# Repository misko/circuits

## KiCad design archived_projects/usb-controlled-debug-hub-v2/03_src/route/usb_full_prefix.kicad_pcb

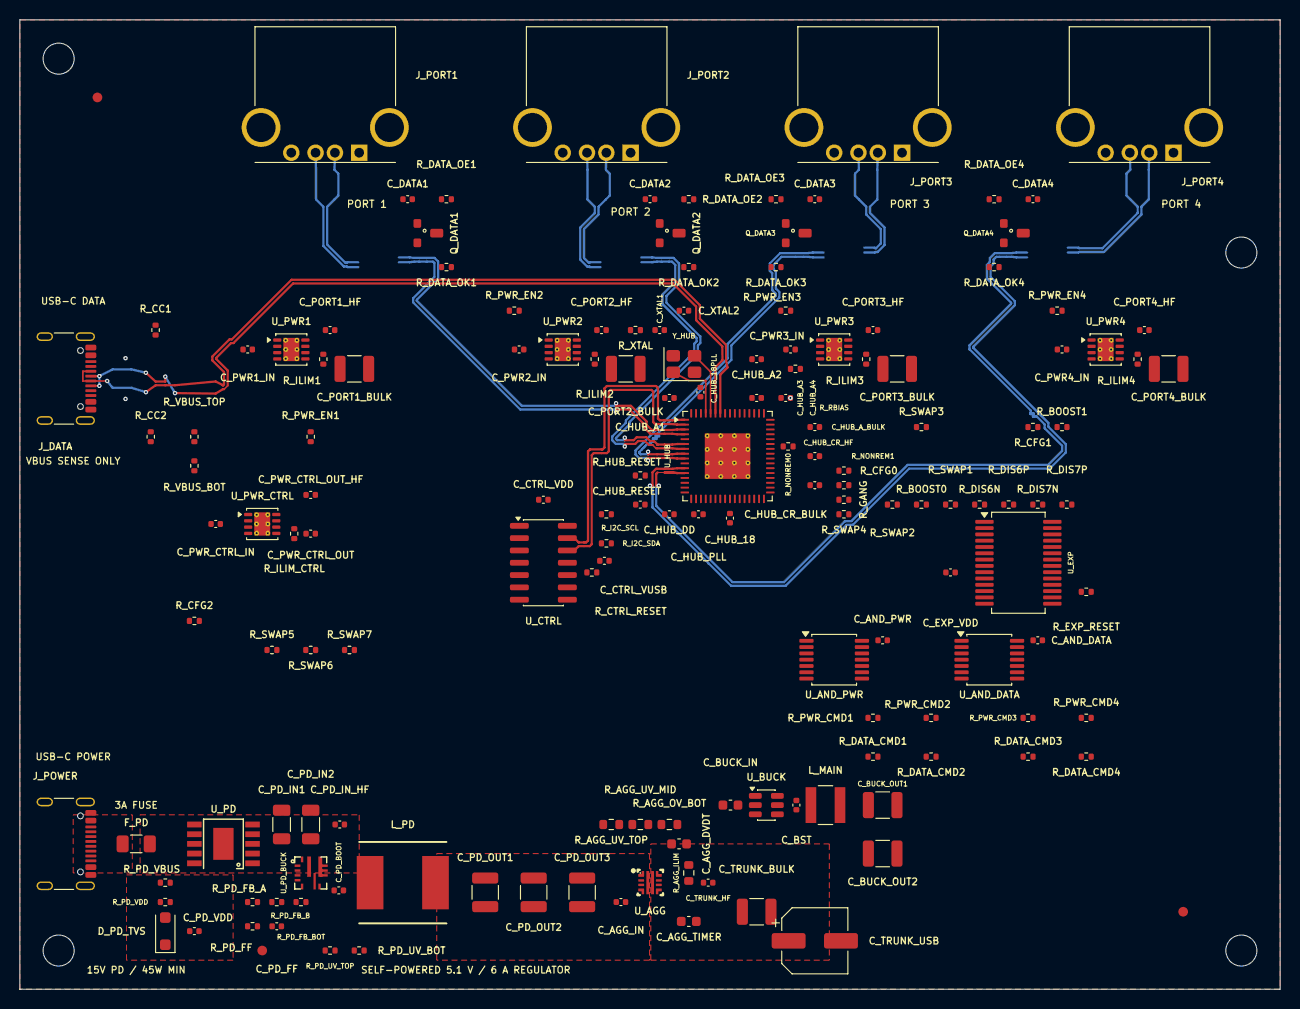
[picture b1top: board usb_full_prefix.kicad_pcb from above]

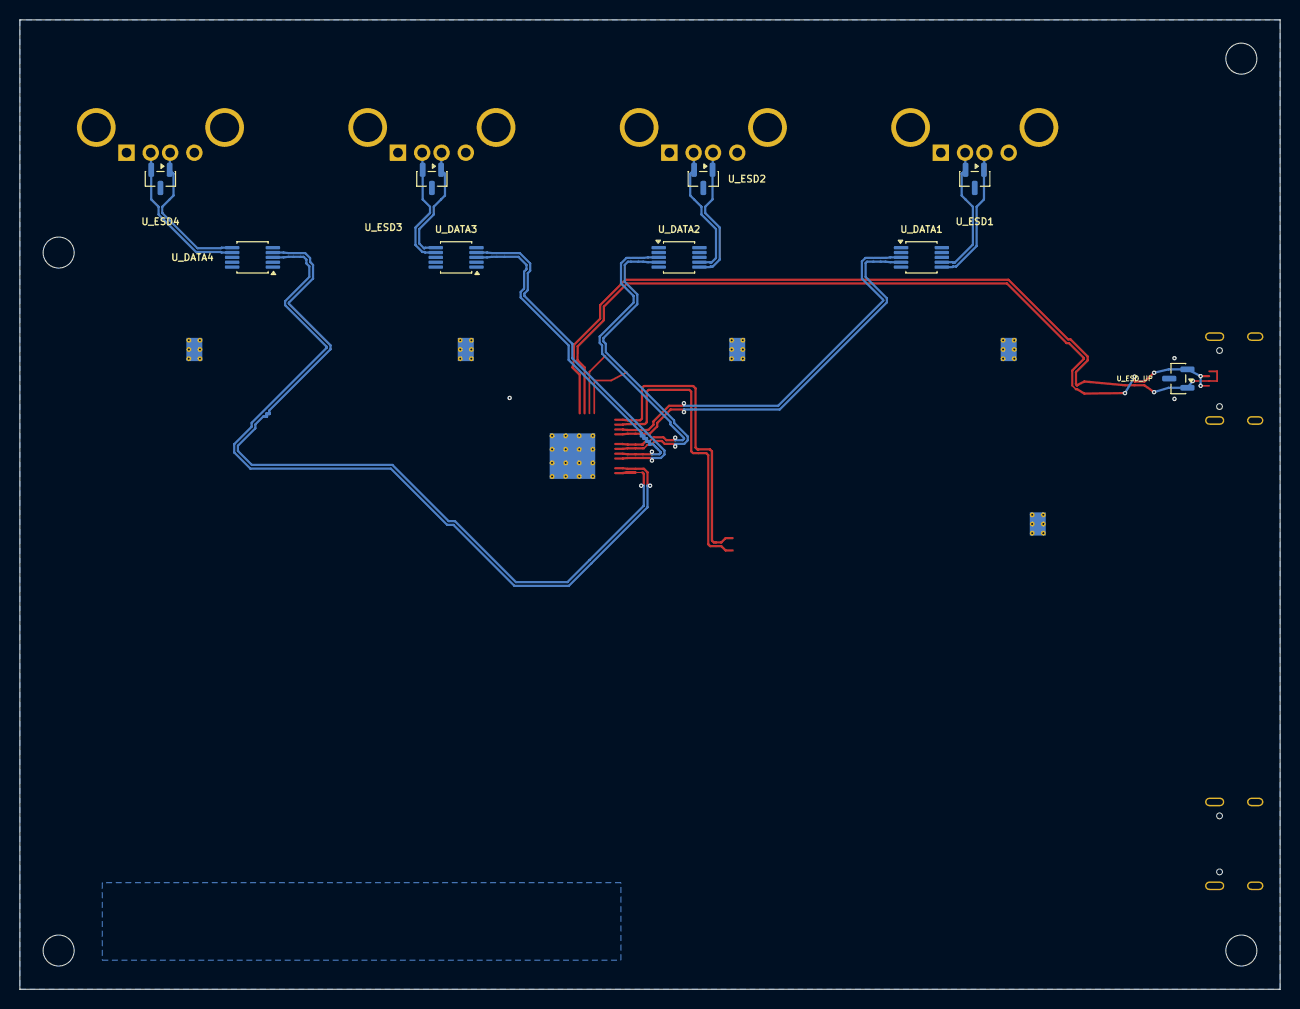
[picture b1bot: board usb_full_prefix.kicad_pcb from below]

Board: 4 copper layers, 130.0 x 100.0 mm, 169 parts (9 on the bottom side), 117 nets.

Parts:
C_AGG_DVDT: 3.3nF; C_0603_1608Metric
C_AGG_IN: 100nF; C_0402_1005Metric
C_AGG_TIMER: 3.3nF; C_0603_1608Metric
C_AND_DATA: 100nF; C_0402_1005Metric
C_AND_PWR: 100nF; C_0402_1005Metric
C_BST: 100nF; C_0402_1005Metric
C_BUCK_IN: 10uF; C_0603_1608Metric
C_BUCK_OUT1, C_BUCK_OUT2: 22uF; C_1210_3225Metric
C_CTRL_VDD: 100nF; C_0402_1005Metric
C_CTRL_VUSB: 330nF; C_0402_1005Metric
C_DATA1, C_DATA2, C_DATA3, C_DATA4: 100nF; C_0402_1005Metric
C_EXP_VDD: 100nF; C_0402_1005Metric
C_HUB_18, C_HUB_18PLL: 1uF; C_0402_1005Metric
C_HUB_A1, C_HUB_A2, C_HUB_A3, C_HUB_A4: 100nF; C_0402_1005Metric
C_HUB_A_BULK: 1uF; C_0402_1005Metric
C_HUB_CR_BULK: 1uF; C_0402_1005Metric
C_HUB_CR_HF: 100nF; C_0402_1005Metric
C_HUB_DD: 100nF; C_0402_1005Metric
C_HUB_PLL: 100nF; C_0402_1005Metric
C_HUB_RESET: 1uF; C_0402_1005Metric
C_PD_BOOT: 100nF; C_0402_1005Metric
C_PD_FF: 100pF; C_0402_1005Metric
C_PD_IN1, C_PD_IN2: 10uF; C_1206_3216Metric
C_PD_IN_HF: 100nF; C_0402_1005Metric
C_PD_OUT1, C_PD_OUT2, C_PD_OUT3: 22uF; C_1210_3225Metric
C_PD_VDD: 1uF; C_0402_1005Metric
C_PORT1_BULK, C_PORT2_BULK, C_PORT3_BULK, C_PORT4_BULK: 22uF; C_1210_3225Metric
C_PORT1_HF, C_PORT2_HF, C_PORT3_HF, C_PORT4_HF: 100nF; C_0402_1005Metric
C_PWR1_IN, C_PWR2_IN, C_PWR3_IN, C_PWR4_IN: 100nF; C_0402_1005Metric
C_PWR_CTRL_IN: 100nF; C_0402_1005Metric
C_PWR_CTRL_OUT: 1uF; C_0402_1005Metric
C_PWR_CTRL_OUT_HF: 100nF; C_0402_1005Metric
C_TRUNK_BULK: 22uF; C_1210_3225Metric
C_TRUNK_HF: 100nF; C_0402_1005Metric
C_TRUNK_USB: 180uF; CP_Elec_6.3x5.8
C_XTAL1, C_XTAL2: 18pF; C_0402_1005Metric
D_PD_TVS: C207257; D_SOD-123F
FID1, FID2, FID3: Fiducial_1mm_Mask2mm
F_PD: C14165; Fuse_1206_3216Metric
H1, H2, H3, H4: MountingHole_3.2mm_M3
J_DATA: C165948; TYPE-C-31-M-12_Datasheet
J_PORT1, J_PORT2, J_PORT3, J_PORT4: C503996; KH-AF90DIP-112_Horizontal
J_POWER: C165948; TYPE-C-31-M-12_Datasheet
L_MAIN: C15269; Sunlord_SWPA4030S
L_PD: C17700166; Sunlord_MWSA0804S
Q_DATA1, Q_DATA2, Q_DATA3, Q_DATA4: C85047; Diodes_SOT23_2N7002K
R_AGG_ILIM: 1kΩ; R_0603_1608Metric
R_AGG_OV_BOT: 43.2kΩ; R_0603_1608Metric
R_AGG_UV_MID: 10kΩ; R_0603_1608Metric
R_AGG_UV_TOP: 150kΩ; R_0603_1608Metric
R_BOOST0, R_BOOST1: 10kΩ; R_0402_1005Metric
R_CC1, R_CC2: 5.1kΩ; R_0402_1005Metric
R_CFG0, R_CFG1, R_CFG2: 10kΩ; R_0402_1005Metric
R_CTRL_RESET: 10kΩ; R_0402_1005Metric
R_DATA_CMD1, R_DATA_CMD2, R_DATA_CMD3, R_DATA_CMD4: 10kΩ; R_0402_1005Metric
R_DATA_OE1, R_DATA_OE2, R_DATA_OE3, R_DATA_OE4: 10kΩ; R_0402_1005Metric
R_DATA_OK1, R_DATA_OK2, R_DATA_OK3, R_DATA_OK4: 10kΩ; R_0402_1005Metric
R_DIS6N, R_DIS6P, R_DIS7N, R_DIS7P: 10kΩ; R_0402_1005Metric
R_EXP_RESET: 10kΩ; R_0402_1005Metric
R_GANG: 10kΩ; R_0402_1005Metric
R_HUB_RESET: 10kΩ; R_0402_1005Metric
R_I2C_SCL, R_I2C_SDA: 4.7kΩ; R_0402_1005Metric
R_ILIM1, R_ILIM2, R_ILIM3, R_ILIM4: 165kΩ; R_0402_1005Metric
R_ILIM_CTRL: 165kΩ; R_0402_1005Metric
R_NONREM0, R_NONREM1: 10kΩ; R_0402_1005Metric
R_PD_FB_A: 75kΩ; R_0402_1005Metric
R_PD_FB_B: 499Ω; R_0402_1005Metric
R_PD_FB_BOT: 10kΩ; R_0402_1005Metric
R_PD_FF: 20kΩ; R_0402_1005Metric
R_PD_UV_BOT: 27.4kΩ; R_0402_1005Metric
R_PD_UV_TOP: 200kΩ; R_0402_1005Metric
R_PD_VBUS: 10kΩ; R_0402_1005Metric
R_PD_VDD: 1kΩ; R_0402_1005Metric
R_PWR_CMD1, R_PWR_CMD2, R_PWR_CMD3, R_PWR_CMD4: 10kΩ; R_0402_1005Metric
R_PWR_EN1, R_PWR_EN2, R_PWR_EN3, R_PWR_EN4: 10kΩ; R_0402_1005Metric
R_RBIAS: 12kΩ; R_0402_1005Metric
R_SWAP1, R_SWAP2, R_SWAP3, R_SWAP4, R_SWAP5, R_SWAP6, R_SWAP7: 100kΩ; R_0402_1005Metric
R_VBUS_BOT: 100kΩ; R_0402_1005Metric
R_VBUS_TOP: 47kΩ; R_0402_1005Metric
R_XTAL: 1MΩ; R_0402_1005Metric
U_AGG: C2864845; TI_RPW0010A_VQFN-HR-10_2x2mm_P0.45mm
U_AND_DATA: C6053; TSSOP-14_4.4x5mm_P0.65mm
U_AND_PWR: C6053; TSSOP-14_4.4x5mm_P0.65mm
U_BUCK: C5248536; TSOT-23-6
U_CTRL: C640876; SOIC-14_3.9x8.7mm_P1.27mm
U_DATA1, U_DATA2, U_DATA3, U_DATA4: C11355; MSOP-10_3x3mm_P0.5mm
U_ESD1, U_ESD2, U_ESD3, U_ESD4: C3708426; SOT-23
U_ESD_UP: C3708426; SOT-23
U_EXP: C558584; SSOP-28_5.3x10.2mm_P0.65mm
U_HUB: C478081; QFN-64-1EP_9x9mm_P0.5mm_EP4.7x4.7mm_ThermalVias
U_PD: C970725; WCH_CH224K_ESSOP10_EP
U_PD_BUCK: C841386; TI_RPA0010A_VQFN-HR-10_3x3mm
U_PWR1, U_PWR2, U_PWR3, U_PWR4: C130056; VSON-8-1EP_3x3mm_P0.65mm_EP1.65x2.4mm_ThermalVias
U_PWR_CTRL: C130056; VSON-8-1EP_3x3mm_P0.65mm_EP1.65x2.4mm_ThermalVias
Y_HUB: C1985204; Crystal_SMD_3225-4Pin_3.2x2.5mm

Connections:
3V3_MAIN: C_AND_DATA.1, C_AND_PWR.1, C_BUCK_OUT1.1, C_BUCK_OUT2.1, C_DATA1.1, C_DATA2.1, C_DATA3.1, C_DATA4.1, C_HUB_A1.1, C_HUB_A2.1, C_HUB_A3.1, C_HUB_A4.1, C_HUB_A_BULK.1, C_HUB_CR_BULK.1, C_HUB_CR_HF.1, C_HUB_DD.1, C_HUB_PLL.1, L_MAIN.2, R_DATA_OE1.1, R_DATA_OE2.1, R_DATA_OE3.1, R_DATA_OE4.1, R_DIS6N.1, R_DIS6P.1, R_DIS7N.1, R_DIS7P.1, R_HUB_RESET.1, R_NONREM0.1, R_SWAP1.2, U_AND_DATA.14, U_AND_PWR.14, U_BUCK.1, U_DATA1.1, U_DATA2.1, U_DATA3.1, U_DATA4.1, U_HUB.5, U_HUB.10, U_HUB.24, U_HUB.46, U_HUB.52, U_HUB.57, U_HUB.64
AGG_DVDT: C_AGG_DVDT.1, U_AGG.7
AGG_ILIM: R_AGG_ILIM.1, U_AGG.9
AGG_OV: R_AGG_OV_BOT.1, R_AGG_UV_MID.2, U_AGG.2
AGG_TIMER: C_AGG_TIMER.1, U_AGG.10
AGG_UV: R_AGG_UV_MID.1, R_AGG_UV_TOP.2, U_AGG.1
BST_3V3: C_BST.1, U_BUCK.6
CTRL_RESET_N: R_CTRL_RESET.2, U_CTRL.4
CTRL_VUSB_3V3: C_CTRL_VUSB.1, U_CTRL.11
DATA_CC1: J_DATA.A5, R_CC1.1
DATA_CC2: J_DATA.B5, R_CC2.1
DATA_CMD1: R_DATA_CMD1.1, U_AND_DATA.2, U_EXP.25
DATA_CMD2: R_DATA_CMD2.1, U_AND_DATA.5, U_EXP.26
DATA_CMD3: R_DATA_CMD3.1, U_AND_DATA.10, U_EXP.27
DATA_CMD4: R_DATA_CMD4.1, U_AND_DATA.13, U_EXP.28
DATA_OE1_N: Q_DATA1.3, R_DATA_OE1.2, U_DATA1.10
DATA_OE2_N: Q_DATA2.3, R_DATA_OE2.2, U_DATA2.10
DATA_OE3_N: Q_DATA3.3, R_DATA_OE3.2, U_DATA3.10
DATA_OE4_N: Q_DATA4.3, R_DATA_OE4.2, U_DATA4.10
DATA_OK1: Q_DATA1.1, R_DATA_OK1.1, U_AND_DATA.3
DATA_OK2: Q_DATA2.1, R_DATA_OK2.1, U_AND_DATA.6
DATA_OK3: Q_DATA3.1, R_DATA_OK3.1, U_AND_DATA.8
DATA_OK4: Q_DATA4.1, R_DATA_OK4.1, U_AND_DATA.11
EXP_RESET_N: R_EXP_RESET.2, U_EXP.18
GND: C_AGG_DVDT.2, C_AGG_IN.2, C_AGG_TIMER.2, C_AND_DATA.2, C_AND_PWR.2, C_BUCK_IN.2, C_BUCK_OUT1.2, C_BUCK_OUT2.2, C_CTRL_VDD.2, C_CTRL_VUSB.2, C_DATA1.2, C_DATA2.2, C_DATA3.2, C_DATA4.2, C_EXP_VDD.2, C_HUB_18.2, C_HUB_18PLL.2, C_HUB_A1.2, C_HUB_A2.2, C_HUB_A3.2, C_HUB_A4.2, C_HUB_A_BULK.2, C_HUB_CR_BULK.2, C_HUB_CR_HF.2, C_HUB_DD.2, C_HUB_PLL.2, C_HUB_RESET.2, C_PD_IN1.2, C_PD_IN2.2, C_PD_IN_HF.2, C_PD_OUT1.2, C_PD_OUT2.2, C_PD_OUT3.2, C_PD_VDD.2, C_PORT1_BULK.2, C_PORT1_HF.2, C_PORT2_BULK.2, C_PORT2_HF.2, C_PORT3_BULK.2, C_PORT3_HF.2, C_PORT4_BULK.2, C_PORT4_HF.2, C_PWR1_IN.2, C_PWR2_IN.2, C_PWR3_IN.2, C_PWR4_IN.2, C_PWR_CTRL_IN.2, C_PWR_CTRL_OUT.2, C_PWR_CTRL_OUT_HF.2, C_TRUNK_BULK.2, C_TRUNK_HF.2, C_TRUNK_USB.2, C_XTAL1.2, C_XTAL2.2, D_PD_TVS.1, J_DATA.A1, J_DATA.A12, J_DATA.B1, J_DATA.B12, J_DATA.SH, J_PORT1.4, J_PORT1.5, J_PORT2.4, J_PORT2.5, J_PORT3.4, J_PORT3.5, J_PORT4.4, J_PORT4.5, J_POWER.A1, J_POWER.A12, J_POWER.B1, J_POWER.B12, J_POWER.SH, Q_DATA1.2, Q_DATA2.2, Q_DATA3.2, Q_DATA4.2, R_AGG_ILIM.2, R_AGG_OV_BOT.2, R_BOOST0.2, R_BOOST1.2, R_CC1.2, R_CC2.2, R_CFG0.2, R_CFG1.2, R_CFG2.2, R_DATA_CMD1.2, R_DATA_CMD2.2, R_DATA_CMD3.2, R_DATA_CMD4.2, R_DATA_OK1.2, R_DATA_OK2.2, R_DATA_OK3.2, R_DATA_OK4.2, R_GANG.2, R_ILIM1.2, R_ILIM2.2, R_ILIM3.2, R_ILIM4.2, R_ILIM_CTRL.2, R_NONREM1.2, R_PD_FB_BOT.2, R_PD_UV_BOT.2, R_PWR_CMD1.2, R_PWR_CMD2.2, R_PWR_CMD3.2, R_PWR_CMD4.2, R_PWR_EN1.2, R_PWR_EN2.2, R_PWR_EN3.2, R_PWR_EN4.2, R_RBIAS.2, R_SWAP2.2, R_SWAP3.2, R_SWAP4.2, R_SWAP5.2, R_SWAP6.2, R_SWAP7.2, R_VBUS_BOT.2, U_AGG.4, U_AGG.8, U_AND_DATA.7, U_AND_PWR.7, U_BUCK.4, U_CTRL.14, U_DATA1.2, U_DATA1.5, U_DATA2.2, U_DATA2.5, U_DATA3.2, U_DATA3.5, U_DATA4.2, U_DATA4.5, U_ESD1.3, U_ESD2.3, U_ESD3.3, U_ESD4.3, U_ESD_UP.3, U_EXP.10, U_EXP.15, U_EXP.16, U_EXP.17, U_HUB.65, U_PD.9, U_PD.11, U_PD_BUCK.3, U_PD_BUCK.9, U_PD_BUCK.10, U_PWR1.1, U_PWR1.9, U_PWR2.1, U_PWR2.9, U_PWR3.1, U_PWR3.9, U_PWR4.1, U_PWR4.9, U_PWR_CTRL.1, U_PWR_CTRL.9, Y_HUB.2, Y_HUB.4
HUB_BOOST0: R_BOOST0.1, U_HUB.50
HUB_BOOST1: R_BOOST1.1, U_HUB.48
HUB_CFG0: R_CFG0.1, U_HUB.41
HUB_CFG1: R_CFG1.1, U_HUB.42
HUB_CFG2: R_CFG2.1, U_HUB.13
HUB_DIS6_N: R_DIS6N.2, U_HUB.53
HUB_DIS6_P: R_DIS6P.2, U_HUB.54
HUB_DIS7_N: R_DIS7N.2, U_HUB.55
HUB_DIS7_P: R_DIS7P.2, U_HUB.56
HUB_GANG: R_GANG.1, U_HUB.34
HUB_NONREM0: R_NONREM0.2, U_HUB.45
HUB_NONREM1: R_NONREM1.1, U_HUB.40
HUB_OCS1_N: U_HUB.28, U_PWR_CTRL.8
HUB_OCS2_N: U_HUB.27, U_PWR1.8
HUB_OCS3_N: U_HUB.22, U_PWR2.8
HUB_OCS4_N: U_HUB.21, U_PWR3.8
HUB_OCS5_N: U_HUB.35, U_PWR4.8
HUB_PRTPWR1: U_HUB.29, U_PWR_CTRL.4
HUB_PRTPWR2: U_AND_PWR.1, U_HUB.26
HUB_PRTPWR3: U_AND_PWR.4, U_HUB.23
HUB_PRTPWR4: U_AND_PWR.9, U_HUB.20
HUB_PRTPWR5: U_AND_PWR.12, U_HUB.30
HUB_RESET_N: C_HUB_RESET.1, R_HUB_RESET.2, U_HUB.43
HUB_SWAP1: R_SWAP1.1, U_HUB.51
HUB_SWAP2: R_SWAP2.1, U_HUB.49
HUB_SWAP3: R_SWAP3.1, U_HUB.47
HUB_SWAP4: R_SWAP4.1, U_HUB.33
HUB_SWAP5: R_SWAP5.1, U_HUB.31
HUB_SWAP6: R_SWAP6.1, U_HUB.17
HUB_SWAP7: R_SWAP7.1, U_HUB.15
HUB_VBUS_SENSE: R_VBUS_BOT.1, R_VBUS_TOP.2, U_HUB.44
HUB_VDD18: C_HUB_18.1, U_HUB.25
HUB_VDD18PLL: C_HUB_18PLL.1, U_HUB.62
I2C_SCL: R_I2C_SCL.2, U_CTRL.10, U_EXP.12
I2C_SDA: R_I2C_SDA.2, U_CTRL.9, U_EXP.13
ILIM1: R_ILIM1.1, U_PWR1.5
ILIM2: R_ILIM2.1, U_PWR2.5
ILIM3: R_ILIM3.1, U_PWR3.5
ILIM4: R_ILIM4.1, U_PWR4.5
ILIM_CTRL: R_ILIM_CTRL.1, U_PWR_CTRL.5
MGMT_N: U_CTRL.12, U_HUB.2
MGMT_P: U_CTRL.13, U_HUB.1
P1_HUB_N: U_DATA1.3, U_HUB.3
P1_HUB_P: U_DATA1.4, U_HUB.4
P1_PORT_N: J_PORT1.2, U_DATA1.7, U_ESD1.2
P1_PORT_P: J_PORT1.3, U_DATA1.6, U_ESD1.1
P2_HUB_N: U_DATA2.3, U_HUB.6
P2_HUB_P: U_DATA2.4, U_HUB.7
P2_PORT_N: J_PORT2.2, U_DATA2.7, U_ESD2.2
P2_PORT_P: J_PORT2.3, U_DATA2.6, U_ESD2.1
P3_HUB_N: U_DATA3.3, U_HUB.8
P3_HUB_P: U_DATA3.4, U_HUB.9
P3_PORT_N: J_PORT3.2, U_DATA3.7, U_ESD3.2
P3_PORT_P: J_PORT3.3, U_DATA3.6, U_ESD3.1
P4_HUB_N: U_DATA4.3, U_HUB.11
P4_HUB_P: U_DATA4.4, U_HUB.12
P4_PORT_N: J_PORT4.2, U_DATA4.7, U_ESD4.2
P4_PORT_P: J_PORT4.3, U_DATA4.6, U_ESD4.1
P5V_PROTECTED: C_BUCK_IN.1, C_PWR1_IN.1, C_PWR2_IN.1, C_PWR3_IN.1, C_PWR4_IN.1, C_PWR_CTRL_IN.1, C_TRUNK_BULK.1, C_TRUNK_HF.1, C_TRUNK_USB.1, U_AGG.6, U_BUCK.2, U_BUCK.3, U_PWR1.2, U_PWR1.3, U_PWR2.2, U_PWR2.3, U_PWR3.2, U_PWR3.3, U_PWR4.2, U_PWR4.3, U_PWR_CTRL.2, U_PWR_CTRL.3
P5V_REG: C_AGG_IN.1, C_PD_OUT1.1, C_PD_OUT2.1, C_PD_OUT3.1, L_PD.2, R_AGG_UV_TOP.1, R_PD_FB_A.1, R_PD_FF.1, U_AGG.5
PD_BOOT: C_PD_BOOT.1, U_PD_BUCK.7
PD_BUCK_EN: R_PD_UV_BOT.1, R_PD_UV_TOP.2, U_PD_BUCK.1
PD_CC1: J_POWER.A5, U_PD.7
PD_CC2: J_POWER.B5, U_PD.6
PD_FB: C_PD_FF.2, R_PD_FB_B.2, R_PD_FB_BOT.1, U_PD_BUCK.2
PD_FB_TOP: R_PD_FB_A.2, R_PD_FB_B.1
PD_FF: C_PD_FF.1, R_PD_FF.2
PD_SW: C_PD_BOOT.2, L_PD.1, U_PD_BUCK.6
PD_VBUS_SENSE: R_PD_VBUS.2, U_PD.8
PD_VDD: C_PD_VDD.1, R_PD_VDD.2, U_PD.1, U_PD.2, U_PD.3
PWR_CMD1: R_PWR_CMD1.1, U_AND_PWR.2, U_EXP.21
PWR_CMD2: R_PWR_CMD2.1, U_AND_PWR.5, U_EXP.22
PWR_CMD3: R_PWR_CMD3.1, U_AND_PWR.10, U_EXP.23
PWR_CMD4: R_PWR_CMD4.1, U_AND_PWR.13, U_EXP.24
PWR_EN1: R_PWR_EN1.1, U_AND_DATA.1, U_AND_PWR.3, U_PWR1.4
PWR_EN2: R_PWR_EN2.1, U_AND_DATA.4, U_AND_PWR.6, U_PWR2.4
PWR_EN3: R_PWR_EN3.1, U_AND_DATA.9, U_AND_PWR.8, U_PWR3.4
PWR_EN4: R_PWR_EN4.1, U_AND_DATA.12, U_AND_PWR.11, U_PWR4.4
RBIAS: R_RBIAS.1, U_HUB.63
SW_3V3: C_BST.2, L_MAIN.1, U_BUCK.5
UP_HUB_N: J_DATA.A7, J_DATA.B7, U_ESD_UP.1, U_HUB.58
UP_HUB_P: J_DATA.A6, J_DATA.B6, U_ESD_UP.2, U_HUB.59
USB_UP_VBUS: J_DATA.A4, J_DATA.A9, J_DATA.B4, J_DATA.B9, R_VBUS_TOP.1
VBUS1_SW: C_PORT1_BULK.1, C_PORT1_HF.1, J_PORT1.1, U_PWR1.6, U_PWR1.7
VBUS2_SW: C_PORT2_BULK.1, C_PORT2_HF.1, J_PORT2.1, U_PWR2.6, U_PWR2.7
VBUS3_SW: C_PORT3_BULK.1, C_PORT3_HF.1, J_PORT3.1, U_PWR3.6, U_PWR3.7
VBUS4_SW: C_PORT4_BULK.1, C_PORT4_HF.1, J_PORT4.1, U_PWR4.6, U_PWR4.7
VBUS_CTRL: C_CTRL_VDD.1, C_EXP_VDD.1, C_PWR_CTRL_OUT.1, C_PWR_CTRL_OUT_HF.1, R_CTRL_RESET.1, R_EXP_RESET.1, R_I2C_SCL.1, R_I2C_SDA.1, U_CTRL.1, U_EXP.9, U_PWR_CTRL.6, U_PWR_CTRL.7
VBUS_PD: C_PD_IN1.1, C_PD_IN2.1, C_PD_IN_HF.1, D_PD_TVS.2, F_PD.2, R_PD_UV_TOP.1, R_PD_VBUS.1, R_PD_VDD.1, U_PD_BUCK.8
VBUS_PD_RAW: F_PD.1, J_POWER.A4, J_POWER.A9, J_POWER.B4, J_POWER.B9
XTAL1: C_XTAL1.1, R_XTAL.1, U_HUB.61, Y_HUB.1
XTAL2: C_XTAL2.1, R_XTAL.2, U_HUB.60, Y_HUB.3

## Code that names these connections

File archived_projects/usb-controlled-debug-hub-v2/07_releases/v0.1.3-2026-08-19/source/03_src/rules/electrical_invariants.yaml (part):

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    why: The lower non-removable strap bit is fixed high so physical port 1 is reported non-removable.
  - {assert: series_chain, chain: [VBUS_PD_RAW, F_PD, VBUS_PD], adr: "0013", why: "every USB-C power contact must pass through the 3A high-voltage fuse before the PD controller and buck"}
  - {assert: series_chain, chain: [P5V_REG, U_AGG, P5V_PROTECTED], through: {U_AGG: ["1", "17"]}, adr: "0016", why: "the regulated 5V rail feeds the low-loss aggregate latch-off eFuse directly"}
  - {assert: pin_on_net, pin: "J_DATA.A4", net: USB_UP_VBUS, adr: "0012", why: "USB-C DATA A4 is upstream sense-only VBUS"}
  - {assert: pin_on_net, pin: "J_DATA.A9", net: USB_UP_VBUS, adr: "0012", why: "USB-C DATA A9 is upstream sense-only VBUS"}
  - {assert: pin_on_net, pin: "J_DATA.B4", net: USB_UP_VBUS, adr: "0012", why: "USB-C DATA B4 is upstream sense-only VBUS"}
  - {assert: pin_on_net, pin: "J_DATA.B9", net: USB_UP_VBUS, adr: "0012", why: "USB-C DATA B9 is upstream sense-only VBUS"}
  - {assert: pin_on_net, pin: "R_CC1.1", net: DATA_CC1, adr: "0012", why: "USB-C DATA CC1 has an independent USB default-current sink termination"}
  - {assert: pin_on_net, pin: "R_CC1.2", net: GND, adr: "0012", why: "USB-C DATA CC1 Rd returns to ground"}
  - {assert: pin_on_net, pin: "R_CC2.1", net: DATA_CC2, adr: "0012", why: "USB-C DATA CC2 has an independent USB default-current sink termination"}
  - {assert: pin_on_net, pin: "R_CC2.2", net: GND, adr: "0012", why: "USB-C DATA CC2 Rd returns to ground"}
  - {assert: part_value, part: R_CC1, equals: 5.1k, tolerance_pct: 1, adr: "0012", why: "USB-C sink Rd"}
  - {assert: part_value, part: R_CC2, equals: 5.1k, tolerance_pct: 1, adr: "0012", why: "USB-C sink Rd"}
  - {assert: pin_on_net, pin: "J_DATA.A6", net: UP_HUB_P, adr: "0012", why: "USB-C DATA A6 carries upstream D+"}
  - {assert: pin_on_net, pin: "J_DATA.B6", net: UP_HUB_P, adr: "0012", why: "USB-C DATA B6 carries upstream D+"}
  - {assert: pin_on_net, pin: "J_DATA.A7", net: UP_HUB_N, adr: "0012", why: "USB-C DATA A7 carries upstream D-"}
  - {assert: pin_on_net, pin: "J_DATA.B7", net: UP_HUB_N, adr: "0012", why: "USB-C DATA B7 carries upstream D-"}
  - {assert: pin_on_net, pin: "U_PD.2", net: PD_VDD, adr: "0013", why: "CH224K CFG2 high"}
  - {assert: pin_on_net, pin: "U_PD.3", net: PD_VDD, adr: "0013", why: "CH224K CFG3 high"}
  - {assert: pin_on_net, pin: "U_PD.9", net: GND, adr: "0013", why: "CH224K CFG1 low; K-specific 0/1/1 strap requests 15V"}
  - {assert: pin_on_net, pin: "U_PD.4", net: PD_PROTO, adr: "0014", why: "PD-only CH224K D+ and D- are shorted locally per the controller reference topology"}
  - {assert: pin_on_net, pin: "U_PD.5", net: PD_PROTO, adr: "0014", why: "PD-only CH224K D+ and D- are shorted locally per the controller reference topology"}
  - {assert: series_chain, chain: [VBUS_PD, U_PD_IN, VBUS_PD_SW], through: {U_PD_IN: ["5", "6"]}, adr: "0014", why: "the buck bulk bank must remain behind the negotiated-voltage inrush gate"}
  - {assert: pin_on_net, pin: "C_PD_IN_HF.1", net: VBUS_PD, adr: "0015", why: "the 1uF/50V X7R damping capacitor is the only intentional bulk directly exposed at Type-C attach"}
  - {assert: part_value, part: C_PD_IN_HF, equals: 1uF, tolerance_pct: 10, adr: "0015", why: "TI recommends local input damping while the total directly exposed sink bank remains below 10uF"}
  - {assert: pin_on_net, pin: "D_PD_TVS.1", net: GND, adr: "0015", why: "TVS1800 ground bank pin 1 requires a short return"}
  - {assert: pin_on_net, pin: "D_PD_TVS.2", net: GND, adr: "0015", why: "TVS1800 ground bank pin 2 requires a short return"}
  - {assert: pin_on_net, pin: "D_PD_TVS.3", net: GND, adr: "0015", why: "TVS1800 ground bank pin 3 requires a short return"}
  - {assert: pin_on_net, pin: "D_PD_TVS.4", net: VBUS_PD, adr: "0015", why: "TVS1800 input bank pin 4 clamps the post-fuse PD input"}
  - {assert: pin_on_net, pin: "D_PD_TVS.5", net: VBUS_PD, adr: "0015", why: "TVS1800 input bank pin 5 clamps the post-fuse PD input"}
  - {assert: pin_on_net, pin: "D_PD_TVS.6", net: VBUS_PD, adr: "0015", why: "TVS1800 input bank pin 6 clamps the post-fuse PD input"}
  - {assert: pin_on_net, pin: "D_PD_TVS.7", net: GND, adr: "0015", why: "TVS1800 exposed pad is grounded per TI"}
  - {assert: pin_on_net, pin: "C_PD_IN1.1", net: VBUS_PD_SW, adr: "0014", why: "the first 10uF buck capacitor is disconnected until negotiated-voltage UVLO passes"}
  - {assert: pin_on_net, pin: "C_PD_IN2.1", net: VBUS_PD_SW, adr: "0014", why: "the second 10uF buck capacitor is disconnected until negotiated-voltage UVLO passes"}
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  - {assert: part_value, part: R_PD_FB_A, equals: 73.2k, tolerance_pct: 0.1, adr: "0016", why: "lowers the charged DC ceiling enough to reserve a 100mV transient envelope"}
  - {assert: part_value, part: R_PD_FB_B, equals: 374, tolerance_pct: 0.1, adr: "0016", why: "the stocked precision trim combines with 73.2k/10k to produce the charged 4.92511-5.10424V window"}
  - {assert: part_value, part: R_PD_FB_BOT, equals: 10k, tolerance_pct: 0.1, adr: "0013", why: "precision lower-feedback leg"}
  - {assert: pin_on_net, pin: "R_VBUS_TOP.1", net: USB_UP_VBUS, adr: "0011", why: "the VBUS detector upper leg must sense only the detachable upstream connector VBUS"}
  - {assert: pin_on_net, pin: "R_VBUS_TOP.2", net: HUB_VBUS_SENSE, adr: "0011", why: "the upper divider leg must terminate at USB2517I VBUS_DET"}
  - {assert: pin_on_net, pin: "R_VBUS_BOT.1", net: HUB_VBUS_SENSE, adr: "0011", why: "the lower divider leg must terminate at USB2517I VBUS_DET"}
  - {assert: pin_on_net, pin: "R_VBUS_BOT.2", net: GND, adr: "0011", why: "the lower divider leg must return to ground"}
  - {assert: pin_on_net, pin: "U_HUB.44", net: HUB_VBUS_SENSE, adr: "0011", why: "USB2517I VBUS_DET must observe the tolerance-checked upstream divider"}
  - {assert: part_value, part: R_VBUS_TOP, equals: 47k, tolerance_pct: 1, adr: "0011", why: "with the 100kohm lower leg this guarantees VBUS_DET high at 4.5V despite resistor tolerance and 10uA sink leakage"}
  - {assert: part_value, part: R_VBUS_BOT, equals: 100k, tolerance_pct: 1, adr: "0011", why: "with the 47kohm upper leg this bounds leakage and VBUS_DET voltage across the 4.5V to 5.5V input range"}
  - assert: net_has_part
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    min: 1
    adr: "0002"
    why: The protected input trunk requires local bulk and high-frequency decoupling.
  - {assert: pin_on_net, pin: "U_AGG.1", net: P5V_REG, adr: "0016", why: "aggregate breaker perimeter input must follow the local 5V regulator"}
  - {assert: pin_on_net, pin: "U_AGG.16", net: P5V_REG, adr: "0016", why: "all aggregate perimeter input lands must carry the local 5V regulator rail"}
  - {assert: pin_on_net, pin: "U_AGG.25", net: P5V_REG, adr: "0016", why: "the split IN PowerPAD must carry the local 5V regulator rail"}
  - {assert: pin_on_net, pin: "U_AGG.17", net: P5V_PROTECTED, adr: "0016", why: "all loads must be downstream of the aggregate breaker"}
  - {assert: pin_on_net, pin: "U_AGG.24", net: P5V_PROTECTED, adr: "0016", why: "all aggregate output perimeter lands must feed the protected rail"}
  - {assert: pin_on_net, pin: "U_AGG.26", net: GND, adr: "0016", why: "the split GND PowerPAD and its Type-VII thermal field require a ground connection"}
  - {assert: pin_on_net, pin: "U_AGG.6", net: P5V_REG, adr: "0016", why: "EN/UVLO is tied directly to IN for the 5V-only aggregate stage"}
  - {assert: pin_on_net, pin: "U_AGG.10", net: GND, adr: "0016", why: "RETRY_DLY grounded selects latch-off"}
  - {assert: pin_on_net, pin: "U_AGG.11", net: GND, adr: "0016", why: "NRETRY is grounded for the latch-off configuration"}
  - {assert: pin_on_net, pin: "U_AGG.12", net: GND, adr: "0016", why: "LDSTRT grounded disables load-detect handshake"}
  - {assert: pin_on_net, pin: "C_AGG_IN.1", net: P5V_REG, adr: "0013", why: "the datasheet-required aggregate-eFuse input bypass must terminate at IN rather than after the switch"}
  - {assert: pin_on_net, pin: "C_AGG_IN.2", net: GND, adr: "0006", why: "the aggregate-eFuse input bypass requires a short local ground return"}
  - {assert: part_value, part: C_AGG_IN, equals: 100nF, tolerance_pct: 10, adr: "0006", why: "TI requires at least 0.1uF directly from IN to GND"}
  - {assert: pin_on_net, pin: "C_TRUNK_USB.1", net: P5V_PROTECTED, adr: "0006", why: "the polarized USB hub bulk capacitor positive terminal must be on the protected trunk"}
  - {assert: pin_on_net, pin: "C_TRUNK_USB.2", net: GND, adr: "0006", why: "the polarized USB hub bulk capacitor negative terminal must be grounded"}
  - {assert: part_value, part: R_AGG_ILIM, equals: 300, tolerance_pct: 1, adr: "0016", why: "uses TPS25980's characterized row and programs the charged 4.2745..5.7755A aggregate threshold"}
  - {assert: part_value, part: C_AGG_TIMER, equals: 6.8nF, tolerance_pct: 5, adr: "0016", why: "bounds TPS25980 aggregate overload blanking to approximately 1.61..6.65ms"}
  - {assert: part_value, part: C_AGG_DVDT, equals: 3.3nF, tolerance_pct: 5, adr: "0016", why: "bounds nominal startup slew to about 1.394V/ms and charged maximum-bank inrush below 0.371A"}
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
